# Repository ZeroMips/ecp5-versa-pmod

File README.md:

# ecp5-versa-pmod

Three Pmod host ports for the Lattice **ECP5 Versa** development board, plugged onto its expansion header **X4**.
A generic adapter, built so that the 1BitSquared **12-bit DVI Pmod** (a dual-wide module) fits exactly on two adjacent ports.
Rev A, designed 2026-11-12, built and tested (see [Commissioning](#commissioning)). Open source hardware.

Rev A built and plugged onto the ECP5 Versa (X4), with the 12-bit DVI Pmod on ports A and B:

| Item | Value |
|---|---|
| Board | 67.0 x 42.5 mm, 2 layers, 1.6 mm FR-4, rounded corners, no mounting holes (it hangs on the 2x20 socket) |
| J1 | 2x20 female socket 2.54 mm on the **bottom**, onto X4; stand-off = socket height (8.5 mm) above the X4 header body |
| J2, J3, J4 | Pmod ports A, B, C: 2x6 female right-angle sockets on the edge that lies over the Versa board edge, 22.86 mm (0.90 in) apart, near pin row 10.16 mm (0.40 in) from the edge, exactly as in the Pmod Interface Specification 1.3.1 figure 5 |
| Signals | X4 IO0..7 on port A, IO8..15 on port B, IO16..23 on port C, 33 ohm series resistor in every line (R1..R24, 0603) |
| Power | 3V3 from X4 pin 20 through F1 (0.5 A PTC) to all ports; 10 uF + 3 x 100 nF; green LED |
| Unused | X4 IO24..28, RESOUT#, CARDSEL# (not connected) |

## Files

| Path | Content |
|---|---|
| `ecp5-versa-pmod.kicad_pro`, `.kicad_sch`, `.kicad_pcb` | the design (KiCad 10); `lib/` holds the project symbol and footprint libraries, `fp-lib-table` / `sym-lib-table` point to them |
| `tools/generate.py` | wrote rev A from the pin tables in it (schematic, board, libraries); kept for reproducibility, from now on edit the KiCad files |
| `tools/check.py` | compares the board nets with the schematic netlist independently of KiCad, checks the DVI Pmod fit, writes `out/pinmap.csv` |
| `tools/release.sh` | ERC, DRC with schematic parity, the check above, schematic PDF, BOM, Gerbers + drill + placement, 1:1 fit-check PDF, STEP, renders |
| `out/` | everything `release.sh` produces: `ecp5-versa-pmod-gerber.zip`, `bom.csv`, `ecp5-versa-pmod-pos.csv`, `ecp5-versa-pmod-schematic.pdf`, `ecp5-versa-pmod-fitcheck-top-1to1.pdf`, `pinmap.csv`, `erc.rpt`, `drc.rpt`, STEP |
| `preview/` | `top.png`, `bottom.png`, `iso.png` |
| `docs/notes.md` | the facts about the Versa, the Pmod specification and the DVI Pmod that the design rests on, with sources |

The schematic is one A3 sheet drawn with wires: X4 on the left with IO0..IO23 on its right side in order (grouped per
port) and 3V3, GND and the unused pins on its left; the 24 series resistors in two staggered columns; the three ports
on the right with their signal pins in connector column order (1, 7, 2, 8, ...), so every X4 pin pair ends on two
adjacent port pins and no wire crosses another; the power section (F1, rails, C1..C4, LED) below X4.

State of rev A: ERC 0, DRC 0 (all severities, schematic parity included), 0 unconnected, netlist cross-check 0 mismatches.

```sh
sh tools/release.sh          # verify and regenerate all outputs (kicad-cli 10)
python3 tools/generate.py    # regenerate the KiCad files from the tables (python3 with KiCad 10 pcbnew)
```

## How it sits on the Versa

X4 runs along the Versa's top edge (the edge opposite the PCIe fingers), about 1 mm from it, with X3 25 mm further in.
X4 pin 1 is at the left end in the row nearer X3 (triangle on the Versa silkscreen), so the even pins face the board edge.
The adapter plugs on with its component side up, `X4 pin 1` marked bottom left; its port edge then lies over the Versa's
board edge and the modules hang outside the Versa, coplanar, about 11 mm above the Versa's surface. The adapter extends
2.8 mm beyond X4 toward X3 (X3 is 25 mm away) and 14 mm beyond the right end of X4, which is beyond the Versa's right edge.
Nothing of the Versa is in the way of a module on any port.

Reverse insertion (adapter rotated 180 degrees on X4) is harmless: the adapter's 3V3 lands on IO16, its GND pins on GND
pins, and its signal lines on IO17..27, CARDSEL# and GND pins through the series resistors. The ports just stay dead.

## Pin map (generated, `out/pinmap.csv`)

Pins 5 and 11 of every port are GND, pins 6 and 12 are 3V3. Pins 1..6 are the upper row (farther from the Versa edge),
7..12 the lower row; pin 1 is at the left end of the upper row when the Versa edge is at the top.

| Port | Pmod pin | X4 pin | X4 signal | FPGA ball | ECP5 pad | Pair | DVI Pmod (A+B) |
|---|---|---|---|---|---|---|---|
| A | 1 | 3 | IO0 | A12 | PT49A | with pin 7 (PT49) | R3 |
| A | 2 | 5 | IO2 | B13 | PT51A | with pin 8 (PT51) | R1 |
| A | 3 | 7 | IO4 | D13 | PT53A | with pin 9 (PT53) | G3 |
| A | 4 | 9 | IO6 | A14 | PT56A | with pin 10 (PT56) | G1 |
| A | 7 | 4 | IO1 | A13 | PT49B | with pin 1 (PT49) | R2 |
| A | 8 | 6 | IO3 | C13 | PT51B | with pin 2 (PT51) | R0 |
| A | 9 | 8 | IO5 | E13 | PT53B | with pin 3 (PT53) | G2 |
| A | 10 | 10 | IO7 | C14 | PT56B | with pin 4 (PT56) | G0 |
| B | 1 | 11 | IO8 | D14 | PT58A | with pin 7 (PT58) | B3 |
| B | 2 | 13 | IO10 | D11 | PT42A/PCLKT1_1 | no pair | CLK |
| B | 3 | 15 | IO12 | A9 | PT33A/GR_PCLK0_1 | with pin 9 (PT33) | B0 |
| B | 4 | 17 | IO14 | D12 | PT47A/GR_PCLK1_0 | with pin 10 (PT47) | HS |
| B | 7 | 12 | IO9 | E14 | PT58B | with pin 1 (PT58) | B2 |
| B | 8 | 14 | IO11 | C10 | PT31B | no pair | B1 |
| B | 9 | 16 | IO13 | B10 | PT33B/GR_PCLK0_0 | with pin 3 (PT33) | DE |
| B | 10 | 18 | IO15 | E12 | PT47B/GR_PCLK1_1 | with pin 4 (PT47) | VS |
| C | 1 | 21 | IO16 | B15 | PT69A | with pin 7 (PT69) |  |
| C | 2 | 25 | IO18 | D15 | PT71A | with pin 8 (PT71) |  |
| C | 3 | 28 | IO20 | A16 | PT74A | with pin 9 (PT74) |  |
| C | 4 | 31 | IO22 | C16 | PT76A | with pin 10 (PT76) |  |
| C | 7 | 23 | IO17 | C15 | PT69B | with pin 1 (PT69) |  |
| C | 8 | 27 | IO19 | E15 | PT71B | with pin 2 (PT71) |  |
| C | 9 | 29 | IO21 | B16 | PT74B | with pin 3 (PT74) |  |
| C | 10 | 32 | IO23 | D16 | PT76B | with pin 4 (PT76) |  |

Each port column (n, n+6) is one ECP5 differential pair with the true half (PIOA) on pin n, except port B column 2
(IO10/IO11). IO10 on port B pin 2 is `PCLKT1_1`, a primary clock input: use port B pin 2 for a Pmod that supplies a clock.
IO12..15 are general-routing clock inputs. All X4 IOs are 3.3 V LVCMOS (banks 0 and 1 of the LFE5UM-45F).

Any gateware pin assignment is allowed; `docs/notes.md` has the balls as a LiteX/Amaranth style connector table.

## Design notes

- **Why column pairs.** The X4 pin pairs (3,4), (5,6) ... are ECP5 A/B pairs, so wiring one X4 pair to one Pmod column
  gives differential-capable columns with every line on the top layer and no vias. Digilent's digital high-speed ports pair
  pins 1-2 instead; that would need a second routing layer under the signals and was not worth it.
- **33 ohm series resistors** (not Digilent's 200 ohm): source termination that works for the 25 MHz DVI pixel bus and for
  faster modules (HyperRAM), while still limiting the current of an accidental driver conflict. 0 ohm or 200 ohm fit the
  same footprint.
- **F1, 0.5 A PTC.** X4 has a single 3V3 pin. Three modules at the specification's ~100 mA stay below the hold current; a
  shorted module trips F1 instead of dragging the Versa's rail. About 50 mV drop at 100 mA.
- **3V3 feed.** X4 pin 20 sits in the inner row, so the feed has to pass between two socket pads (0.84 mm gap). It
  leaves on both layers at 0.4 mm, the widest the gap allows, and both copies run along the bottom edge (where no
  signal return current flows) and straight up into F1, 2 x 0.5 mm: no point narrower than the trunk.
- **Ground.** Pours on both layers; the X4 socket's eight GND pins are tied together by a 0.4 mm track on the bottom
  (no pour fits between 2.54 mm pins), the port GND pins have thermal reliefs.
- **Series resistors at the FPGA end** (right above X4), doglegs at 60 degrees so the three bundles never cross.
- **Silkscreen.** Top: port names, pin 1/7 marks, the X4 IO numbers of every signal column, GND/3V3, the X4 pin 1 corner,
  the F1 and LED labels. Bottom: the full pin table with FPGA balls, the X4 pin 1 corner. OSHW logo on both sides.
  All labels are generated from the same table as the netlist.

## 12-bit DVI Pmod (1BitSquared, hardware v1.1a)

Module J2 (LiteX slot "a": R3 R1 G3 G1 / R2 R0 G2 G0) goes on **port A**, module J1 (slot "b": B3 CLK B0 HS / B2 B1 DE VS)
on **port B**; ports B+C work the same way. The module's connectors are 22.89 mm apart, the adapter's 22.86 mm (0.03 mm,
nothing at 2.54 mm pitch); `tools/check.py` recomputes this from the module's PCB coordinates. The module then hangs
40 mm beyond the Versa edge, its HDMI jack away from the Versa. The last column of the table above gives the module
signal on every adapter pin.

## Parts (`out/bom.csv`; LCSC numbers also in the schematic fields)

LCSC is the JLCPCB assembly source. The Reichelt and Conrad columns are the parts actually ordered for hand assembly
(prices as ordered, 2026-11). The Reichelt parts are substitutes with the same value and package, not the same manufacturer parts.

| Ref | Part | LCSC | Reichelt (qty, price) | Conrad |
|---|---|---|---|---|
| R1..R24 | 33 ohm 1% 0603 | C23140 (UNI-ROYAL 0603WAF330JT5E) | VIS CRCW060333R, 100 mW (50, 0,04 EUR) | |
| R25 | 1 kohm 1% 0603 | C21190 (UNI-ROYAL 0603WAF1001T5E) | WAL WR06X1001FTL, 100 mW (5, 0,02 EUR) | |
| C1 | 10 uF 0805 | C15850 (Samsung CL21A106KAYNNNE, X5R 25 V) | CL21B106KOQNNNE, X7R 16 V, 10 %, 1,25 mm high (5, 0,27 EUR) | |
| C2..C4 | 100 nF 0603 | C14663 (YAGEO CC0603KRX7R9BB104, X7R 50 V) | X7R-G0603 100N, X7R 16 V, 10 % (10, 0,03 EUR) | |
| D1 | green LED 0603 | C72043 (Everlight 19-217/GHC-YR1S2/3T, **Extended**) | LED EL 0603 GR1, 112 mcd, 120 deg (5, 0,07 EUR) | |
| F1 | PTC resettable fuse 1206, Ihold 0.5 A | **not chosen** in the JLCPCB library; C70069 turned out to be a 250 mA part | SMD1206P050TF, 0.5 A, **6 V** (5, 0,14 EUR) | |
| J1 | 2x20 female 2.54 mm, straight | C2977589 (ZHOURI 2.54-2*20, 8.5 mm insulator, 3.2 mm tails) | MPE 094-2-040 (2, 1,10 EUR) | |
| J2..J4 | 2x6 female right angle 2.54 mm | C2897426 (HCTL PM254-2-06-W-8.5) | | econ connect BLW2X6 (Conrad shows 1 St. per item) |

Checked 2026-11-12 for the LCSC parts: R1..R24, C1 and D1 part pages read (Basic/Extended not shown, except D1 is Extended);
R25 and C2..C4 Basic (earlier session); J1 page read, straight socket inferred from "holes direction: top"; J2..J4 page
read (2 rows, 12 pins, right angle, 3 A), the **drawing was not readable**. Any 0603 LED fits D1, the 1 k gives about 0.6 mA.

The Reichelt and Conrad parts above were used for the built and tested rev A board and fit. The JLCPCB-side LCSC parts
were not ordered. The F1 part is rated 6 V, which is enough on the 3.3 V rail but not for a 5 V source; the earlier note
asked for 16 V or more.

LCSC stock and prices were not visible to the tools used. The sockets are through-hole (JLCPCB assembles them only as a
special service, or solder them by hand). Choose the 2x20 socket height to taste; 8.5 mm puts the module 11 mm above
the Versa.

## Commissioning

Rev A was assembled by hand with the Reichelt and Conrad parts listed above and tested on an ECP5 Versa by the author
(2026-11-22): it works. The individual test steps were not recorded. The silkscreen copyright text on the front
(`(c) 2026 Dirk Eibach`, 90 degrees at the left edge) is on the built board (see the photo), but the Gerbers in `out/` were generated before it was added to
the PCB; rerun `tools/release.sh` so that `out/` matches the board.

### Checks before ordering (rev A)

1. Print `out/ecp5-versa-pmod-fitcheck-top-1to1.pdf` at 100 % and lay the DVI Pmod's connectors on it (J2 on A, J1 on B).
2. Compare the sockets with the footprints (right-angle socket: pin rows 2.54 mm apart, near row 10.16 mm from the edge,
   body front flush with the edge; J1 height 8.5 mm). **Done with the built board:** the Conrad BLW2X6 (J2..J4) and the
   Reichelt MPE 094-2-040 (J1) fit. The HCTL PM254-2-06-W-8.5 (C2897426) was not tried. The PTC was picked (SMD1206P050TF).
3. Load `out/ecp5-versa-pmod-gerber.zip` in a Gerber viewer once (it was checked by DRC and by the renders only).
4. Check that the Versa's X4 pin 1 is where `docs/notes.md` says (lower left, square pad with a triangle); if it were in the
   outer row the adapter would have to be mirrored (`tools/generate.py` keeps this in two constants).

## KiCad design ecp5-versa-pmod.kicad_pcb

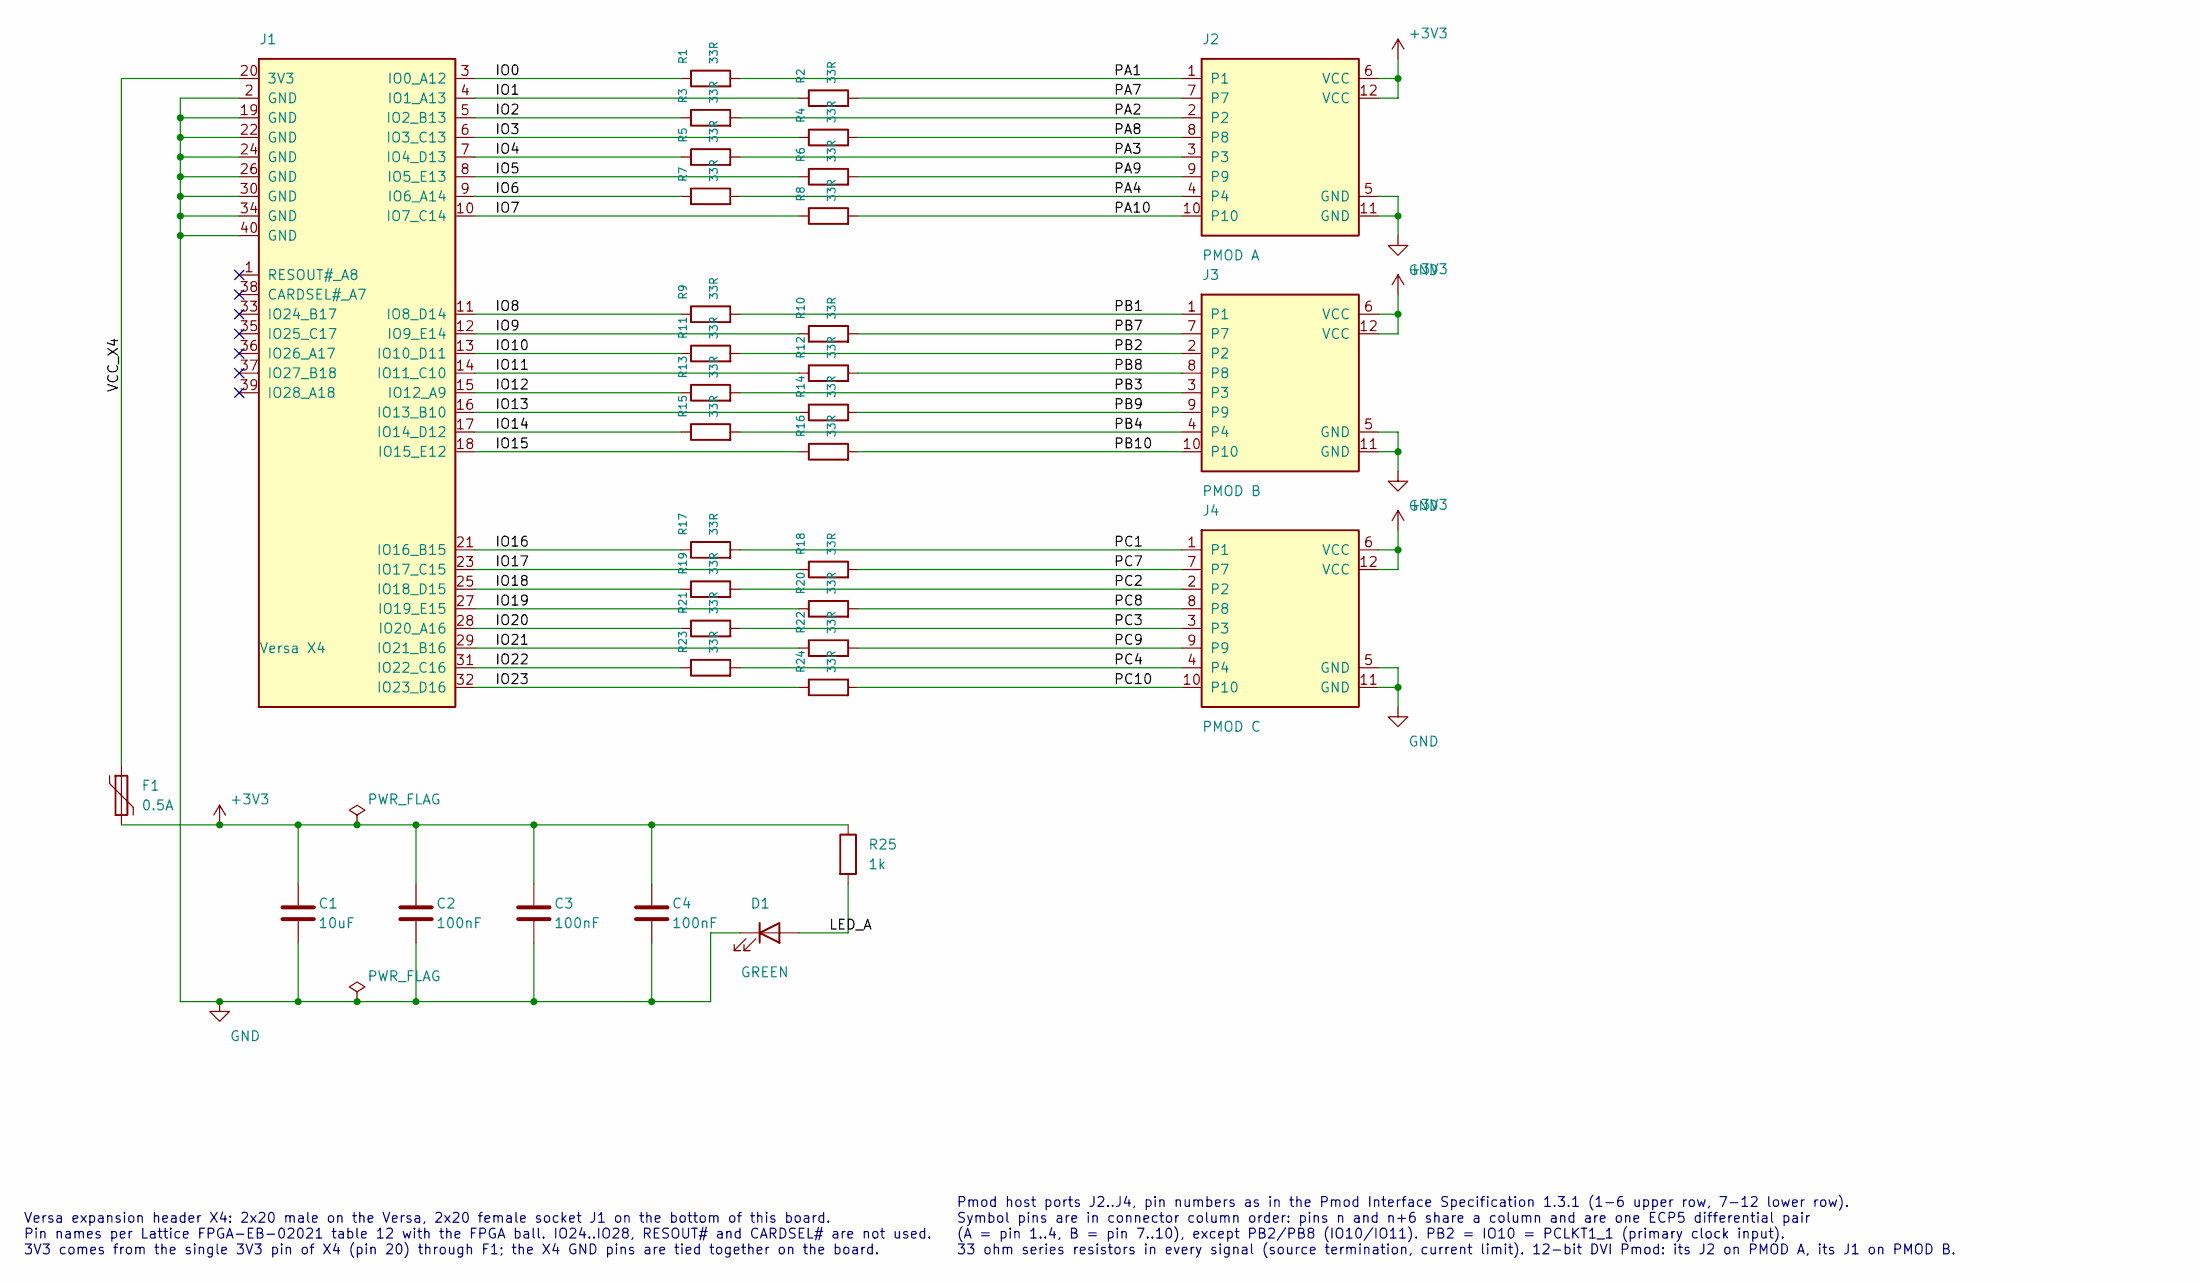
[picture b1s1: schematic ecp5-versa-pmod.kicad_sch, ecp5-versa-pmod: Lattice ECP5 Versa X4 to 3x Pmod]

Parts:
C1: 10uF; C_0805_2012Metric; MPN Samsung CL21A106KAYNNNE; LCSC C15850
C2, C3, C4: 100nF; C_0603_1608Metric; MPN YAGEO CC0603KRX7R9BB104; LCSC C14663
D1: GREEN; LED_0603_1608Metric; MPN Everlight 19-217/GHC-YR1S2/3T; LCSC C72043
F1: 0.5A; Fuse_1206_3216Metric; MPN PTC 1206 Ihold 0.5 A
J1: Versa X4; PinSocket_2x20_P2.54mm_Vertical; MPN ZHOURI 2.54-2*20; LCSC C2977589
J2: PMOD A; Pmod_Host_2x06_Horizontal; MPN HCTL PM254-2-06-W-8.5; LCSC C2897426
J3: PMOD B; Pmod_Host_2x06_Horizontal; MPN HCTL PM254-2-06-W-8.5; LCSC C2897426
J4: PMOD C; Pmod_Host_2x06_Horizontal; MPN HCTL PM254-2-06-W-8.5; LCSC C2897426
R1, R2, R3, R4, R5, R6, R7, R8, R9, R10, R11, R12, R13, R14, R15, R16, R17, R18, R19, R20, R21, R22, R23, R24: 33R; R_0603_1608Metric; MPN UNI-ROYAL 0603WAF330JT5E; LCSC C23140
R25: 1k; R_0603_1608Metric; MPN UNI-ROYAL 0603WAF1001T5E; LCSC C21190

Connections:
+3V3: C1.1, C2.1, C3.1, C4.1, F1.2, J2.6 (VCC), J2.12 (VCC), J3.6 (VCC), J3.12 (VCC), J4.6 (VCC), J4.12 (VCC), R25.1
/IO0: J1.3 (IO0_A12), R1.1
/IO1: J1.4 (IO1_A13), R2.1
/IO2: J1.5 (IO2_B13), R3.1
/IO3: J1.6 (IO3_C13), R4.1
/IO4: J1.7 (IO4_D13), R5.1
/IO5: J1.8 (IO5_E13), R6.1
/IO6: J1.9 (IO6_A14), R7.1
/IO7: J1.10 (IO7_C14), R8.1
/IO8: J1.11 (IO8_D14), R9.1
/IO9: J1.12 (IO9_E14), R10.1
/IO10: J1.13 (IO10_D11), R11.1
/IO11: J1.14 (IO11_C10), R12.1
/IO12: J1.15 (IO12_A9), R13.1
/IO13: J1.16 (IO13_B10), R14.1
/IO14: J1.17 (IO14_D12), R15.1
/IO15: J1.18 (IO15_E12), R16.1
/IO16: J1.21 (IO16_B15), R17.1
/IO17: J1.23 (IO17_C15), R18.1
/IO18: J1.25 (IO18_D15), R19.1
/IO19: J1.27 (IO19_E15), R20.1
/IO20: J1.28 (IO20_A16), R21.1
/IO21: J1.29 (IO21_B16), R22.1
/IO22: J1.31 (IO22_C16), R23.1
/IO23: J1.32 (IO23_D16), R24.1
/LED_A: D1.2 (A), R25.2
/PA1: J2.1, R1.2
/PA2: J2.2, R3.2
/PA3: J2.3, R5.2
/PA4: J2.4, R7.2
/PA7: J2.7, R2.2
/PA8: J2.8, R4.2
/PA9: J2.9, R6.2
/PA10: J2.10, R8.2
/PB1: J3.1, R9.2
/PB2: J3.2, R11.2
/PB3: J3.3, R13.2
/PB4: J3.4, R15.2
/PB7: J3.7, R10.2
/PB8: J3.8, R12.2
/PB9: J3.9, R14.2
/PB10: J3.10, R16.2
/PC1: J4.1, R17.2
/PC2: J4.2, R19.2
/PC3: J4.3, R21.2
/PC4: J4.4, R23.2
/PC7: J4.7, R18.2
/PC8: J4.8, R20.2
/PC9: J4.9, R22.2
/PC10: J4.10, R24.2
/VCC_X4: F1.1, J1.20 (3V3)
GND: C1.2, C2.2, C3.2, C4.2, D1.1 (K), J1.2 (GND), J1.19 (GND), J1.22 (GND), J1.24 (GND), J1.26 (GND), J1.30 (GND), J1.34 (GND), J1.40 (GND), J2.5 (GND), J2.11 (GND), J3.5 (GND), J3.11 (GND), J4.5 (GND), J4.11 (GND)

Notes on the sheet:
Versa expansion header X4: 2x20 male on the Versa, 2x20 female socket J1 on the bottom of this board. Pin names per Lattice FPGA-EB-02021 table 12 with the FPGA ball. IO24..IO28, RESOUT# and CARDSEL# are not used. 3V3 comes from the single 3V3 pin of X4 (pin 20) through F1; the X4 GND pins are tied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
Pmod host ports J2..J4, pin numbers as in the Pmod Interface Specification 1.3.1 (1-6 upper row, 7-12 lower row). Symbol pins are in connector column order: pins n and n+6 share a column and are one ECP5 differential pair (A = pin 1..4, B = pin 7..10), except PB2/PB8 (IO10/IO11). PB2 = IO10 = PCLKT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

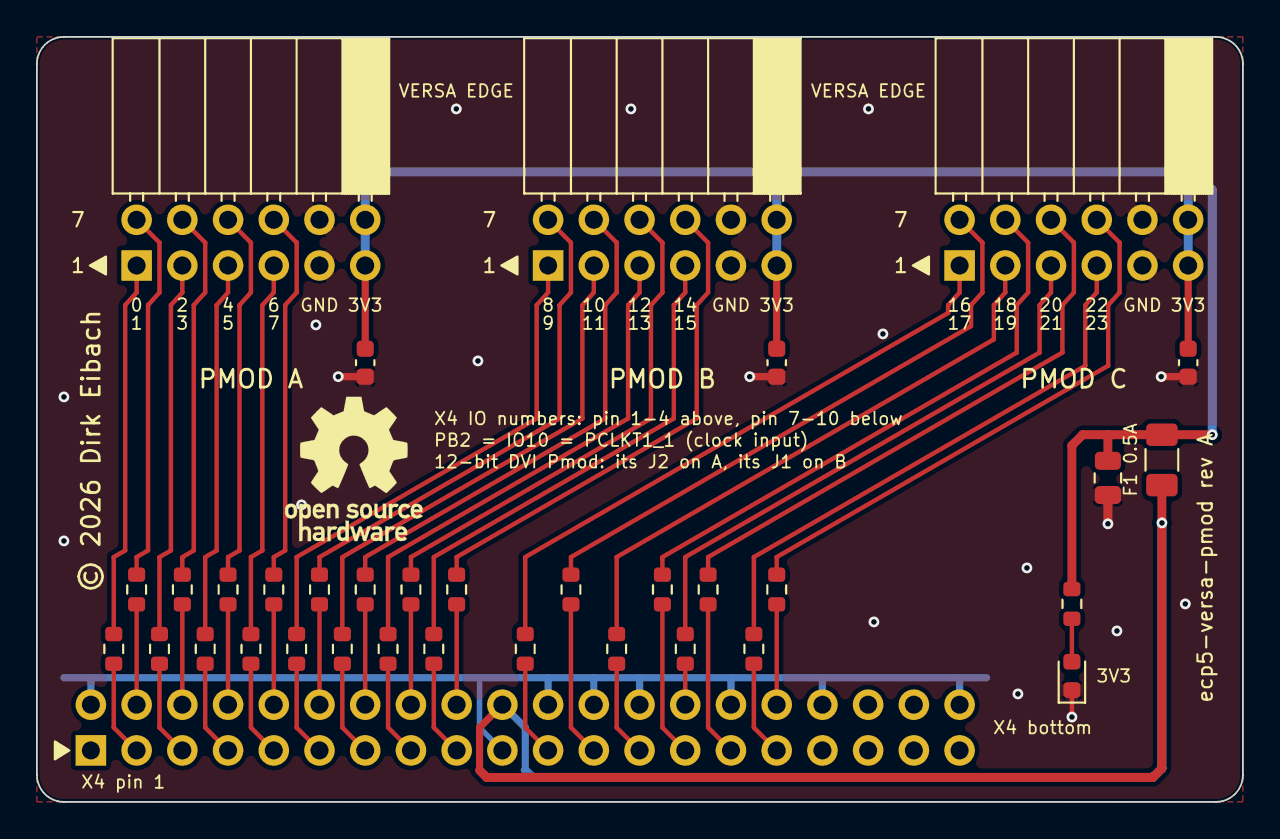
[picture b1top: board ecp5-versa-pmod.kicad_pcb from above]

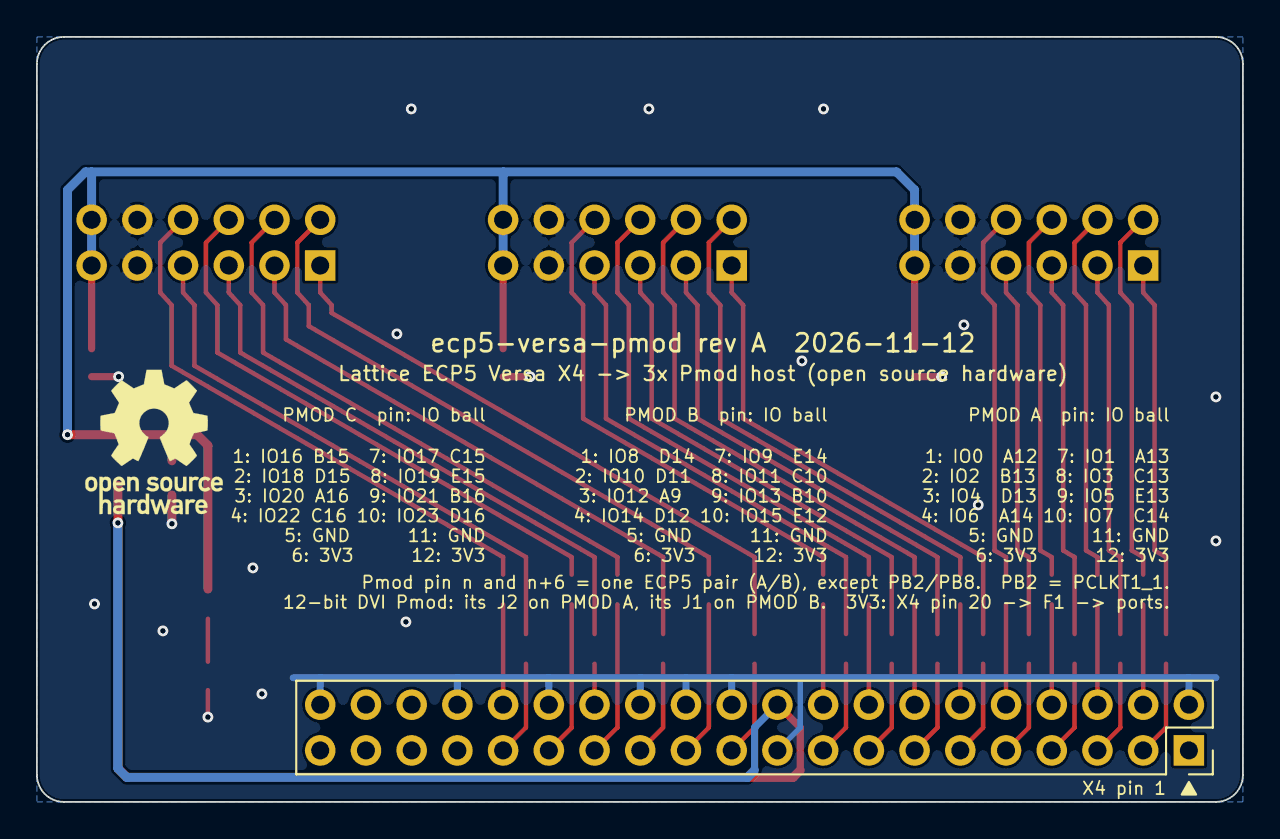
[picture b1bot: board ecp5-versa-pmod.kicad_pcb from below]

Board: 2 copper layers, 67.0 x 42.5 mm, 37 parts (2 on the bottom side), 52 nets.

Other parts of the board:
LOGO1, LOGO2: OSHW-Logo_7.5x8mm_SilkScreen

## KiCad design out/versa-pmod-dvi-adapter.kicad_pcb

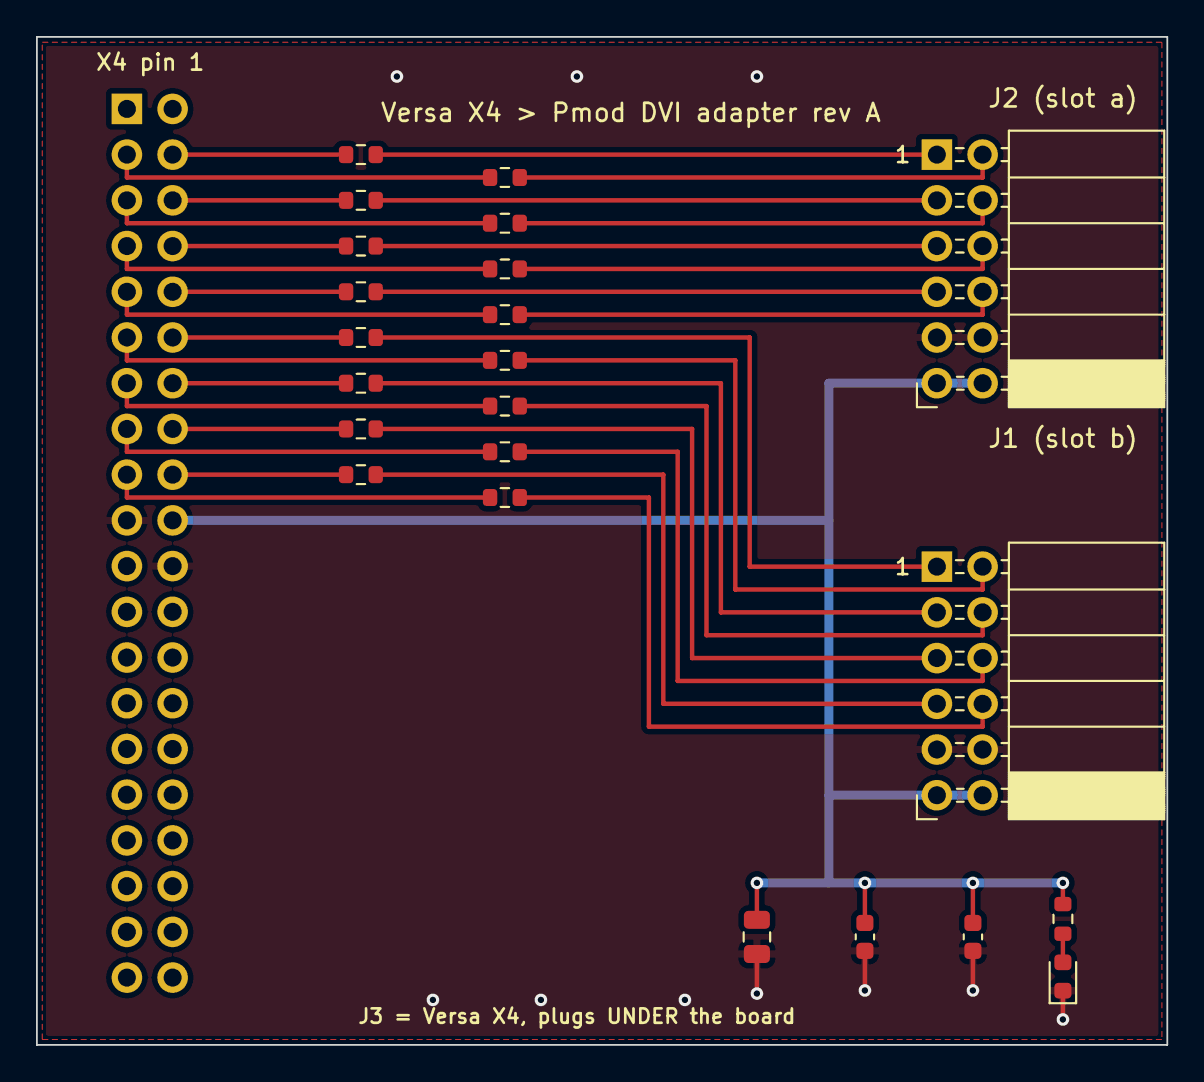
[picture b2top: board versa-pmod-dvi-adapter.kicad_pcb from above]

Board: 2 copper layers, 62.8 x 56.0 mm, 24 parts (1 on the bottom side), 35 nets.

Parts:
C1: 10uF C15850; C_0805_2012Metric
C2, C3: 100nF C14663; C_0603_1608Metric
D1: LED red C2286; LED_0603_1608Metric
J1, J2: 2x6 female RA C2897426; PinSocket_2x06_P2.54mm_Horizontal
J3: 2x20 female 8.5mm C2977589; PinSocket_2x20_P2.54mm_Vertical
R1, R2, R3, R4, R5, R6, R7, R8, R9, R10, R11, R12, R13, R14, R15, R16: 100 C22775; R_0603_1608Metric
R17: 1k C21190; R_0603_1608Metric

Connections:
3V3: C1.2, C2.2, C3.2, J1.6, J1.12, J2.6, J2.12, J3.20, R17.2
DVI_J1_B0: J1.3, R13.2
DVI_J1_B1: J1.8, R12.2
DVI_J1_B2: J1.7, R10.2
DVI_J1_B3: J1.1, R9.2
DVI_J1_CLK: J1.2, R11.2
DVI_J1_DE: J1.9, R14.2
DVI_J1_HS: J1.4, R15.2
DVI_J1_VS: J1.10, R16.2
DVI_J2_G0: J2.10, R8.2
DVI_J2_G1: J2.4, R7.2
DVI_J2_G2: J2.9, R6.2
DVI_J2_G3: J2.3, R5.2
DVI_J2_R0: J2.8, R4.2
DVI_J2_R1: J2.2, R3.2
DVI_J2_R2: J2.7, R2.2
DVI_J2_R3: J2.1, R1.2
GND: C1.1, C2.1, C3.1, D1.1, J1.5, J1.11, J2.5, J2.11, J3.19, J3.22
IO0: J3.3, R2.1
IO1: J3.4, R1.1
IO2: J3.5, R4.1
IO3: J3.6, R3.1
IO4: J3.7, R6.1
IO5: J3.8, R5.1
IO6: J3.9, R8.1
IO7: J3.10, R7.1
IO8: J3.11, R10.1
IO9: J3.12, R9.1
IO10: J3.13, R12.1
IO11: J3.14, R11.1
IO12: J3.15, R14.1
IO13: J3.16, R13.1
IO14: J3.17, R16.1
IO15: J3.18, R15.1
LED_A: D1.2, R17.1

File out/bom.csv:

Designators,Qty,Value,Footprint,LCSC,MPN
C1,1,10uF,C_0805_2012Metric,C15850,CL21A106KAYNNNE (Samsung)
"C2,C3",2,100nF,C_0603_1608Metric,C14663,CC0603KRX7R9BB104 (YAGEO)
D1,1,LED red,LED_0603_1608Metric,C2286,KT-0603R (Hubei KENTO)
"J1,J2",2,2x6 female RA,PinSocket_2x06_P2.54mm_Horizontal,C2897426,PM254-2-06-W-8.5 (HCTL)
J3,1,2x20 female 8.5mm,PinSocket_2x20_P2.54mm_Vertical,C2977589,2.54-2*20 (ZHOURI)
"R1,R2,R3,R4,R5,R6,R7,R8,R9,R10,R11,R12,R13,R14,R15,R16",16,100,R_0603_1608Metric,C22775,0603WAF1000T5E (UNI-ROYAL)
R17,1,1k,R_0603_1608Metric,C21190,0603WAF1001T5E (UNI-ROYAL)

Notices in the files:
ecp5-versa-pmod.kicad_pcb:
© 2026 Dirk Eibach
